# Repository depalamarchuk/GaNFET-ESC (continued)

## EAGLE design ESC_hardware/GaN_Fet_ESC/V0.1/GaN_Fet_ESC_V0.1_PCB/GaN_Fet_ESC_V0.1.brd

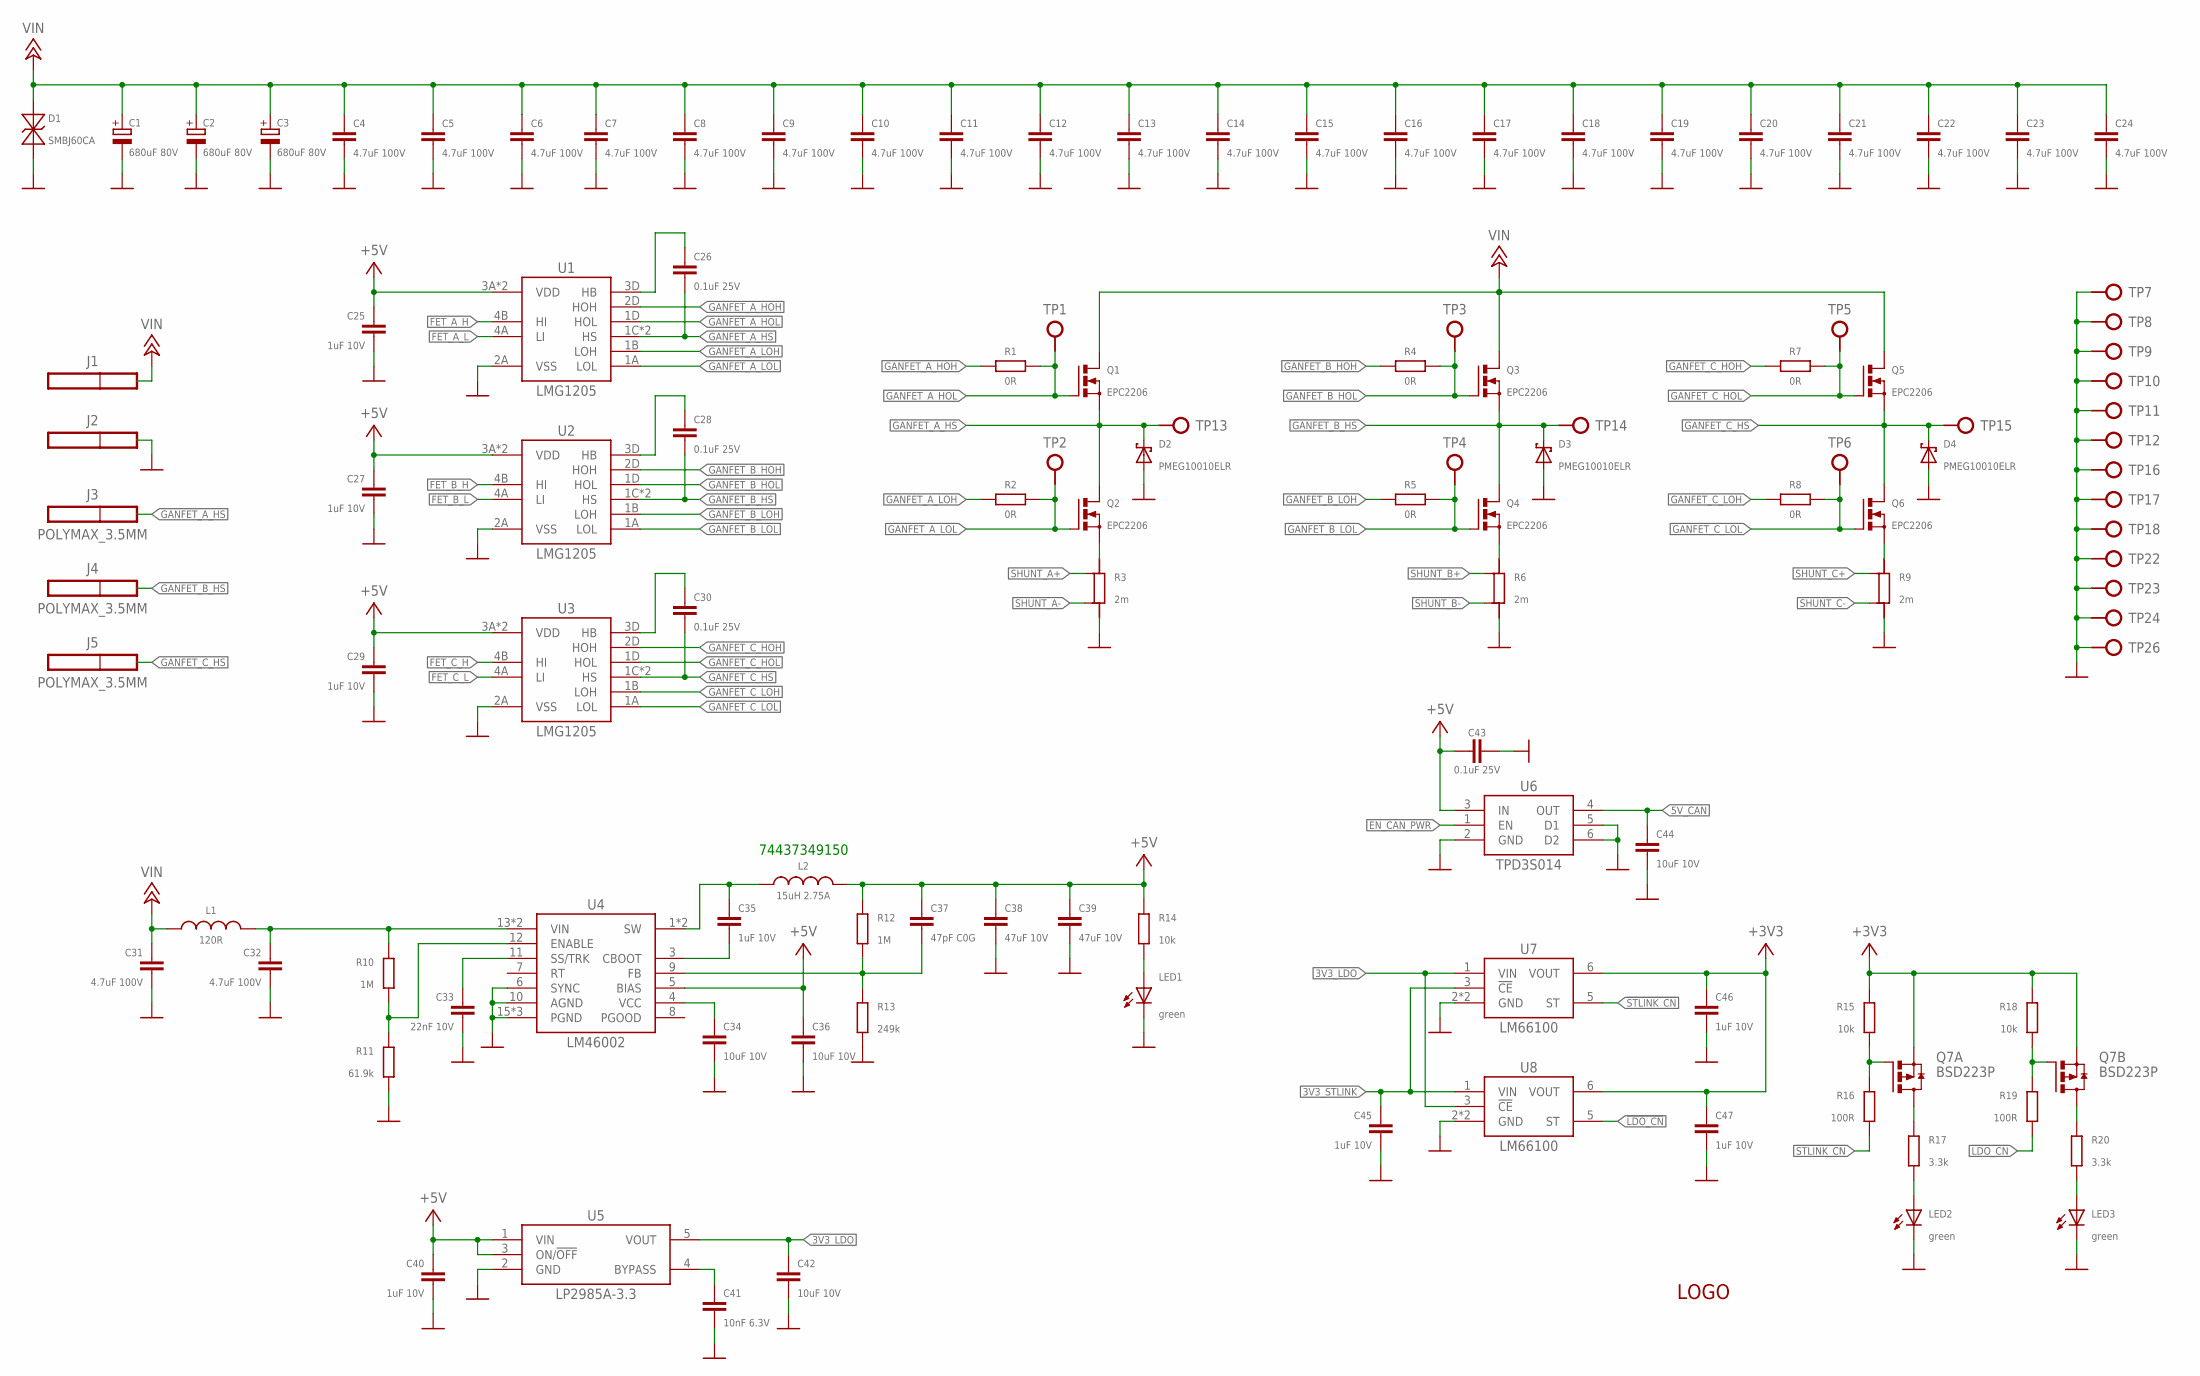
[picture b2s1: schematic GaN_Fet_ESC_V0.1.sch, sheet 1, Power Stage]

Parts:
C1: 680uF 80V; C_7.50_16_26.5_1
C2: 680uF 80V; C_7.50_16_26.5_2
C3: 680uF 80V; C_7.50_16_26.5_3
C4, C5, C6, C7, C8, C9, C10, C11, C12, C13, C14, C15, C16, C17, C18, C19, C20, C21, C22, C23, C24, C31, C32: 4.7uF 100V; C1210
C25, C27, C29, C35, C40, C45, C46, C47: 1uF 10V; C0402
C26, C28, C30, C43: 0.1uF 25V; C0402
C33: 22nF 10V; C0402
C34, C36, C42, C44: 10uF 10V; C0603
C37: 47pF C0G; C0402
C38, C39: 47uF 10V; C1206
C41: 10nF 6.3V; C0402
D1: SMBJ60CA; DO214AA(SMB)
D2, D3, D4: PMEG10010ELR; SOD123F
J1, J2: PIN_14X10; 4X10SMD
J3, J4, J5: POLYMAX_3.5MM
L1: 120R; L1206
L2: 15uH 2.75A; WURTH_6.6X6.6
LED1, LED2, LED3: green; CHIP-LED0603
Q1, Q2, Q3, Q4, Q5, Q6: EPC2206
Q7: BSD223P; SC-70-6
R1, R2, R4, R5, R7, R8: 0R; R0402
R3, R6, R9: 2m; CSS2H-2512
R10: 1M; R0603
R11: 61.9k; R0603
R12: 1M; R0402
R13: 249k; R0402
R14, R15, R18: 10k; R0402
R16, R19: 100R; R0402
R17, R20: 3.3k; R0402
TP1, TP2, TP3, TP4, TP5, TP6, TP13, TP14, TP15: TESTPOINT/0.9MM; 0.9MM
TP7, TP8, TP9, TP10, TP11, TP12, TP16, TP17, TP18, TP22, TP23, TP24, TP26: TESTPOINT0.5MM; 0.5MM
U1, U2, U3: LMG1205
U4: LM46002; TSS0P16-PAD
U5: LP2985A-3.3; SOT-23-5
U6: TPD3S014; SOT-23-6
U7, U8: LM66100; SC-70-6
U$1: LOGO

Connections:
3V3_LDO: C42.1, U5.5 (VOUT), U7.1 (VIN), U8.3 (!CE)
3V3_STLINK: C45.1, U7.3 (!CE), U8.1 (VIN); also elsewhere on the board
5V_CAN: C44.1, U6.4 (OUT); also elsewhere on the board
5V_VCC: C34.1, U4.4 (VCC)
5V_VIN: C32.1, L1.2, R10.2, U4.13 (VIN), U4.14 (VIN)
!LDO_CN: R19.1, U8.5 (ST)
!STLINK_CN: R16.1, U7.5 (ST)
+3V3: C46.1, C47.1, Q7.1 (S), Q7.4 (S), R15.2, R18.2, U7.6 (VOUT), U8.6 (VOUT); also elsewhere on the board
+5V: C25.1, C27.1, C29.1, C36.1, C37.1, C38.1, C39.1, C40.1, C43.1, L2.2, R12.2, R14.2, U1.3A (VDD), U1.4C (VDD), U2.3A (VDD), U2.4C (VDD), U3.3A (VDD), U3.4C (VDD), U4.5 (BIAS), U5.1 (VIN), U5.3 (ON/!OFF), U6.3 (IN); also elsewhere on the board
CBOOT: C35.2, U4.3 (CBOOT)
ENABLE: R10.1, R11.2, U4.12 (ENABLE)
EN_CAN_PWR: U6.1 (EN)
FB: C37.2, R12.1, R13.2, U4.9 (FB)
FET_A_H: U1.4B (HI); also elsewhere on the board
FET_A_L: U1.4A (LI); also elsewhere on the board
FET_B_H: U2.4B (HI); also elsewhere on the board
FET_B_L: U2.4A (LI); also elsewhere on the board
FET_C_H: U3.4B (HI); also elsewhere on the board
FET_C_L: U3.4A (LI); also elsewhere on the board
GANFET_A_HB: C26.1, U1.3D (HB)
GANFET_A_HOH: R1.1, U1.2D (HOH)
GANFET_A_HOL: Q1.1 (G), R1.2, TP1.P$1, U1.1D (HOL)
GANFET_A_HS: C26.2, D2.C, J3.1, Q1.2 (S), Q1.5 (S), Q1.6 (S), Q1.9 (S), Q1.10 (S), Q1.13 (S), Q1.14 (S), Q1.17 (S), Q1.18 (S), Q1.21 (S), Q1.22 (S), Q1.25 (S), Q1.26 (S), Q1.29 (S), Q1.30 (S), Q2.3 (D), Q2.4 (D), Q2.7 (D), Q2.8 (D), Q2.11 (D), Q2.12 (D), Q2.15 (D), Q2.16 (D), Q2.19 (D), Q2.20 (D), Q2.23 (D), Q2.24 (D), Q2.27 (D), Q2.28 (D), TP13.P$1, U1.1C (HS), U1.4D (HS); also elsewhere on the board
GANFET_A_LOH: R2.1, U1.1B (LOH)
GANFET_A_LOL: Q2.1 (G), R2.2, TP2.P$1, U1.1A (LOL)
GANFET_A_SHUNT: Q2.2 (S), Q2.5 (S), Q2.6 (S), Q2.9 (S), Q2.10 (S), Q2.13 (S), Q2.14 (S), Q2.17 (S), Q2.18 (S), Q2.21 (S), Q2.22 (S), Q2.25 (S), Q2.26 (S), Q2.29 (S), Q2.30 (S), R3.1
GANFET_B_HB: C28.1, U2.3D (HB)
GANFET_B_HOH: R4.1, U2.2D (HOH)
GANFET_B_HOL: Q3.1 (G), R4.2, TP3.P$1, U2.1D (HOL)
GANFET_B_HS: C28.2, D3.C, J4.1, Q3.2 (S), Q3.5 (S), Q3.6 (S), Q3.9 (S), Q3.10 (S), Q3.13 (S), Q3.14 (S), Q3.17 (S), Q3.18 (S), Q3.21 (S), Q3.22 (S), Q3.25 (S), Q3.26 (S), Q3.29 (S), Q3.30 (S), Q4.3 (D), Q4.4 (D), Q4.7 (D), Q4.8 (D), Q4.11 (D), Q4.12 (D), Q4.15 (D), Q4.16 (D), Q4.19 (D), Q4.20 (D), Q4.23 (D), Q4.24 (D), Q4.27 (D), Q4.28 (D), TP14.P$1, U2.1C (HS), U2.4D (HS); also elsewhere on the board
GANFET_B_LOH: R5.1, U2.1B (LOH)
GANFET_B_LOL: Q4.1 (G), R5.2, TP4.P$1, U2.1A (LOL)
GANFET_B_SHUNT: Q4.2 (S), Q4.5 (S), Q4.6 (S), Q4.9 (S), Q4.10 (S), Q4.13 (S), Q4.14 (S), Q4.17 (S), Q4.18 (S), Q4.21 (S), Q4.22 (S), Q4.25 (S), Q4.26 (S), Q4.29 (S), Q4.30 (S), R6.1
GANFET_C_HB: C30.1, U3.3D (HB)
GANFET_C_HOH: R7.1, U3.2D (HOH)
GANFET_C_HOL: Q5.1 (G), R7.2, TP5.P$1, U3.1D (HOL)
GANFET_C_HS: C30.2, D4.C, J5.1, Q5.2 (S), Q5.5 (S), Q5.6 (S), Q5.9 (S), Q5.10 (S), Q5.13 (S), Q5.14 (S), Q5.17 (S), Q5.18 (S), Q5.21 (S), Q5.22 (S), Q5.25 (S), Q5.26 (S), Q5.29 (S), Q5.30 (S), Q6.3 (D), Q6.4 (D), Q6.7 (D), Q6.8 (D), Q6.11 (D), Q6.12 (D), Q6.15 (D), Q6.16 (D), Q6.19 (D), Q6.20 (D), Q6.23 (D), Q6.24 (D), Q6.27 (D), Q6.28 (D), TP15.P$1, U3.1C (HS), U3.4D (HS); also elsewhere on the board
GANFET_C_LOH: R8.1, U3.1B (LOH)
GANFET_C_LOL: Q6.1 (G), R8.2, TP6.P$1, U3.1A (LOL)
GANFET_C_SHUNT: Q6.2 (S), Q6.5 (S), Q6.6 (S), Q6.9 (S), Q6.10 (S), Q6.13 (S), Q6.14 (S), Q6.17 (S), Q6.18 (S), Q6.21 (S), Q6.22 (S), Q6.25 (S), Q6.26 (S), Q6.29 (S), Q6.30 (S), R9.1
GND: C1.-, C2.-, C3.-, C4.2, C5.2, C6.2, C7.2, C8.2, C9.2, C10.2, C11.2, C12.2, C13.2, C14.2, C15.2, C16.2, C17.2, C18.2, C19.2, C20.2, C21.2, C22.2, C23.2, C24.2, C25.2, C27.2, C29.2, C31.2, C32.2, C33.2, C34.2, C36.2, C38.2, C39.2, C40.2, C41.2, C42.2, C43.2, C44.2, C45.2, C46.2, C47.2, D1.K (C), D2.A, D3.A, D4.A, J2.1, LED1.C, LED2.C, LED3.C, R3.2, R6.2, R9.2, R11.1, R13.1, TP7.P$1, TP8.P$1, TP9.P$1, TP10.P$1, TP11.P$1, TP12.P$1, TP16.P$1, TP17.P$1, TP18.P$1, TP22.P$1, TP23.P$1, TP24.P$1, TP26.P$1, U1.2A (VSS), U2.2A (VSS), U3.2A (VSS), U4.6 (SYNC), U4.10 (AGND), U4.15 (PGND), U4.16 (PGND), U4.PAD (PGND), U5.2 (GND), U6.2 (GND), U6.5 (D1), U6.6 (D2), U7.2 (GND), U7.4 (GND), U8.2 (GND), U8.4 (GND); also elsewhere on the board
LDO_BYPASS: C41.1, U5.4 (BYPASS)
unnamed: LED3.A, R20.1
unnamed: LED2.A, R17.1
unnamed: LED1.A, R14.1
unnamed: Q7.3 (D), R17.2
unnamed: Q7.6 (D), R20.2
unnamed: Q7.2 (G), R15.1, R16.2
unnamed: Q7.5 (G), R18.1, R19.2
SHUNT_A+: R3.1_SENSE (1K); also elsewhere on the board
SHUNT_A-: R3.2_SENSE (2K); also elsewhere on the board
SHUNT_B+: R6.1_SENSE (1K); also elsewhere on the board
SHUNT_B-: R6.2_SENSE (2K); also elsewhere on the board
SHUNT_C+: R9.1_SENSE (1K); also elsewhere on the board
SHUNT_C-: R9.2_SENSE (2K); also elsewhere on the board
SS: C33.1, U4.11 (SS/TRK)
SW: C35.1, L2.1, U4.1 (SW), U4.2 (SW)
VIN: C1.+, C2.+, C3.+, C4.1, C5.1, C6.1, C7.1, C8.1, C9.1, C10.1, C11.1, C12.1, C13.1, C14.1, C15.1, C16.1, C17.1, C18.1, C19.1, C20.1, C21.1, C22.1, C23.1, C24.1, C31.1, D1.A, J1.1, L1.1, Q1.3 (D), Q1.4 (D), Q1.7 (D), Q1.8 (D), Q1.11 (D), Q1.12 (D), Q1.15 (D), Q1.16 (D), Q1.19 (D), Q1.20 (D), Q1.23 (D), Q1.24 (D), Q1.27 (D), Q1.28 (D), Q3.3 (D), Q3.4 (D), Q3.7 (D), Q3.8 (D), Q3.11 (D), Q3.12 (D), Q3.15 (D), Q3.16 (D), Q3.19 (D), Q3.20 (D), Q3.23 (D), Q3.24 (D), Q3.27 (D), Q3.28 (D), Q5.3 (D), Q5.4 (D), Q5.7 (D), Q5.8 (D), Q5.11 (D), Q5.12 (D), Q5.15 (D), Q5.16 (D), Q5.19 (D), Q5.20 (D), Q5.23 (D), Q5.24 (D), Q5.27 (D), Q5.28 (D); also elsewhere on the board

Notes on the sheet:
74437349150

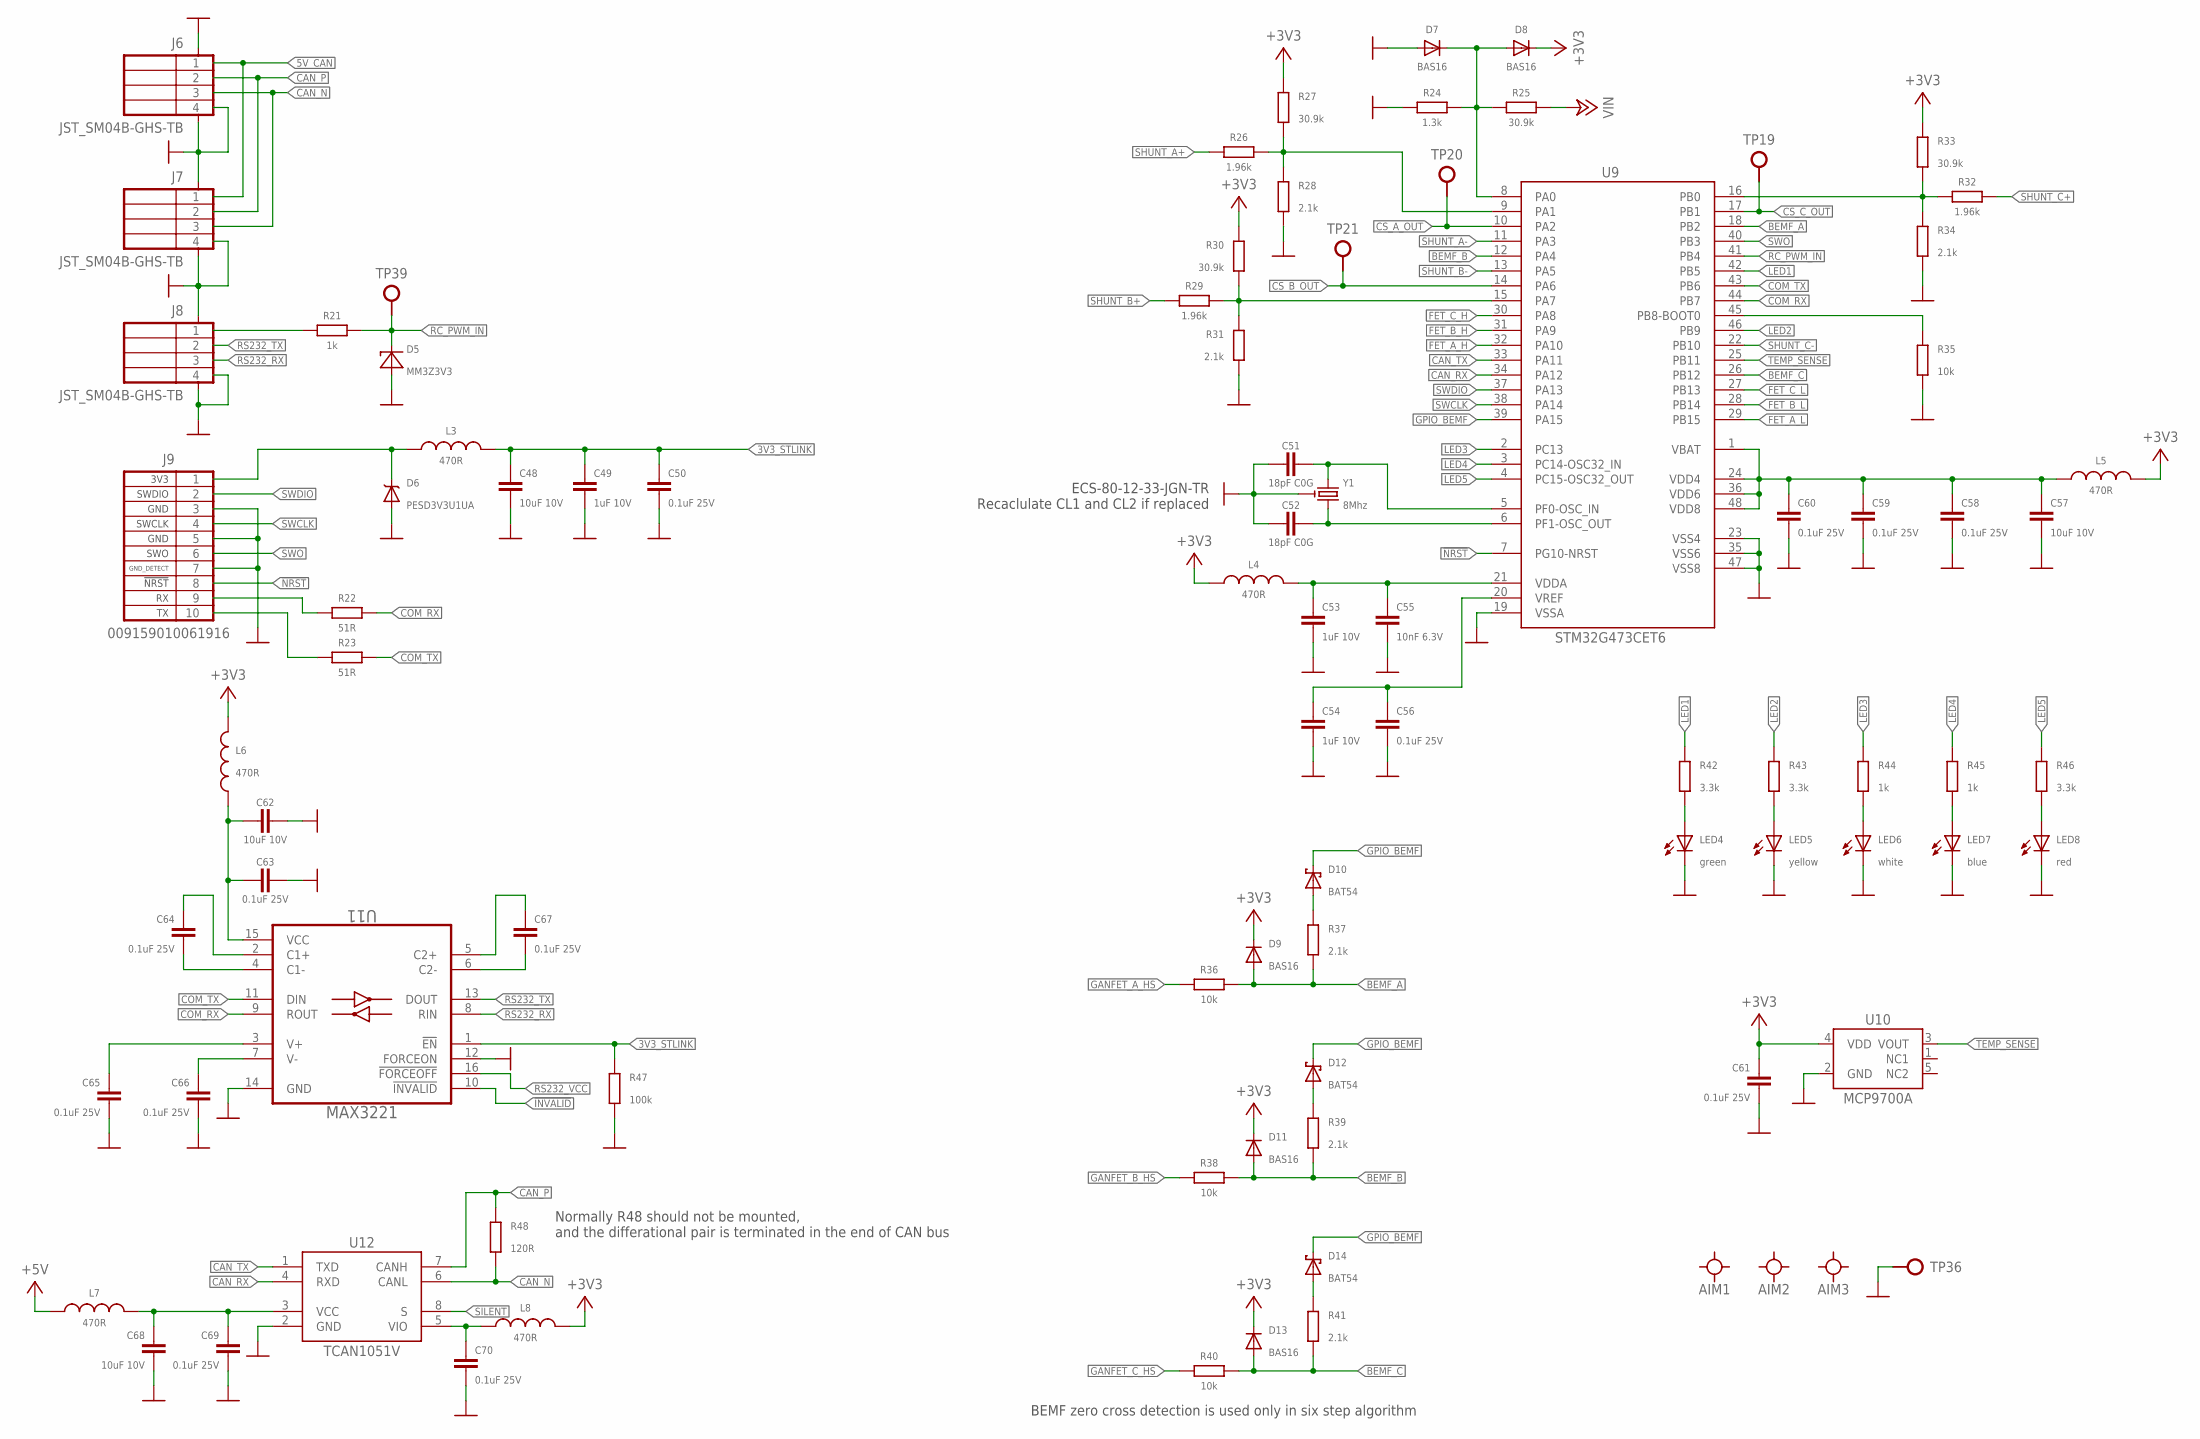
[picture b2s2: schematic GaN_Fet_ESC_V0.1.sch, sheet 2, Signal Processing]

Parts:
AIM1, AIM2, AIM3: AIM_1_MM
C48, C57, C62, C68: 10uF 10V; C0603
C49, C53, C54: 1uF 10V; C0402
C50, C56, C58, C59, C60, C61, C63, C64, C65, C66, C67, C69, C70: 0.1uF 25V; C0402
C51, C52: 18pF C0G; C0402
C55: 10nF 6.3V; C0402
D5: MM3Z3V3; SOD323F
D6: PESD3V3U1UA; SOD323F
D7, D8, D9, D11, D13: BAS16; SOD523
D10, D12, D14: BAT54; SOD523
J6, J7, J8: JST_SM04B-GHS-TB
J9: 009159010061916
L3, L4, L5, L6, L7, L8: 470R; L0603
LED4: green; CHIP-LED0603
LED5: yellow; CHIP-LED0603
LED6: white; CHIP-LED0603
LED7: blue; CHIP-LED0603
LED8: red; CHIP-LED0603
R21, R44, R45: 1k; R0402
R22, R23: 51R; R0402
R24: 1.3k; R0603
R25: 30.9k; R0603
R26, R29, R32: 1.96k; R0402
R27, R30, R33: 30.9k; R0402
R28, R31, R34, R37, R39, R41: 2.1k; R0402
R35, R36, R38, R40: 10k; R0402
R42, R43, R46: 3.3k; R0402
R47: 100k; R0402
R48: 120R; R0805
TP19, TP20, TP21, TP39: TESTPOINT/0.9MM; 0.9MM
TP36: TESTPOINT0.5MM; 0.5MM
U9: STM32G473CET6; LQFP-48
U10: MCP9700A; SC-70-5
U11: MAX3221; TSS0P16
U12: TCAN1051V; SOIC-8
Y1: 8Mhz; CRYSTAL_SMD_3.2X2.5MM

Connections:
3V3_STLINK: C48.1, C49.1, C50.1, L3.1, R47.2, U11.1 (!EN); also elsewhere on the board
5V_CAN: J6.1, J7.1; also elsewhere on the board
!INVALID: U11.10 (!INVALID)
!NRST: J9.8, U9.7 (PG10-NRST)
+3V3: C61.1, D8.C, D9.C, D11.C, D13.C, L4.1, L5.2, L6.1, L8.2, R27.2, R30.2, R33.2, U10.4 (VDD); also elsewhere on the board
+5V: L7.1; also elsewhere on the board
BEMF_A: D9.A, R36.2, R37.1, U9.18 (PB2)
BEMF_B: D11.A, R38.2, R39.1, U9.12 (PA4)
BEMF_C: D13.A, R40.2, R41.1, U9.26 (PB12)
BOOT0: R35.2, U9.45 (PB8-BOOT0)
C1+: C64.1, U11.2 (C1+)
C1-: C64.2, U11.4 (C1-)
C2+: C67.1, U11.5 (C2+)
C2-: C67.2, U11.6 (C2-)
CAN_N: J6.3, J7.3, R48.1, U12.6 (CANL)
CAN_P: J6.2, J7.2, R48.2, U12.7 (CANH)
CAN_RX: U9.34 (PA12), U12.4 (RXD)
CAN_TX: U9.33 (PA11), U12.1 (TXD)
CAN_VCC: C68.1, C69.1, L7.2, U12.3 (VCC)
CAN_VIO: C70.1, L8.1, U12.5 (VIO)
COM_RX: R22.1, U9.44 (PB7), U11.9 (ROUT)
COM_TX: R23.1, U9.43 (PB6), U11.11 (DIN)
CS_A_OUT: TP20.P$1, U9.10 (PA2)
CS_B_OUT: TP21.P$1, U9.14 (PA6)
CS_C_OUT: TP19.P$1, U9.17 (PB1)
FET_A_H: U9.32 (PA10); also elsewhere on the board
FET_A_L: U9.29 (PB15); also elsewhere on the board
FET_B_H: U9.31 (PA9); also elsewhere on the board
FET_B_L: U9.28 (PB14); also elsewhere on the board
FET_C_H: U9.30 (PA8); also elsewhere on the board
FET_C_L: U9.27 (PB13); also elsewhere on the board
GANFET_A_HS: R36.1; also elsewhere on the board
GANFET_B_HS: R38.1; also elsewhere on the board
GANFET_C_HS: R40.1; also elsewhere on the board
GND: C48.2, C49.2, C50.2, C51.1, C52.1, C53.2, C54.2, C55.2, C56.2, C57.2, C58.2, C59.2, C60.2, C61.2, C62.2, C63.2, C65.2, C66.2, C68.2, C69.2, C70.2, D5.A, D6.A, D7.A, J6.4, J6.5, J6.6, J7.4, J7.5, J7.6, J8.4, J8.5, J8.6, J9.3, J9.5, J9.7, LED4.C, LED5.C, LED6.C, LED7.C, LED8.C, R24.1, R28.1, R31.1, R34.1, R35.1, R47.1, TP36.P$1, U9.19 (VSSA), U9.23 (VSS4), U9.35 (VSS6), U9.47 (VSS8), U10.2 (GND), U11.12 (FORCEON), U11.14 (GND), U12.2 (GND), Y1.2 (3), Y1.4 (3); also elsewhere on the board
GPIO_BEMF: D10.C, D12.C, D14.C, U9.39 (PA15)
LED1: R42.2, U9.42 (PB5)
LED2: R43.2, U9.46 (PB9)
LED3: R44.2, U9.2 (PC13)
LED4: R45.2, U9.3 (PC14-OSC32_IN)
LED5: R46.2, U9.4 (PC15-OSC32_OUT)
MCU_VDD: C57.1, C58.1, C59.1, C60.1, L5.1, U9.1 (VBAT), U9.24 (VDD4), U9.36 (VDD6), U9.48 (VDD8)
MCU_VDDA: C53.1, C55.1, L4.2, U9.21 (VDDA)
MCU_VREF: C54.1, C56.1, U9.20 (VREF)
unnamed: LED5.A, R43.1
unnamed: J9.9, R22.2
unnamed: LED4.A, R42.1
unnamed: LED7.A, R45.1
unnamed: LED8.A, R46.1
unnamed: J8.1, R21.2
unnamed: D12.A, R39.2
unnamed: C51.2, U9.5 (PF0-OSC_IN), Y1.1
unnamed: C52.2, U9.6 (PF1-OSC_OUT), Y1.3 (2)
unnamed: D10.A, R37.2
unnamed: D14.A, R41.2
unnamed: D6.C, J9.1, L3.2
unnamed: J9.10, R23.2
unnamed: LED6.A, R44.1
OPAMP1+: R26.2, R27.1, R28.2, U9.9 (PA1)
OPAMP2+: R29.2, R30.1, R31.2, U9.15 (PA7)
OPAMP3+: R32.2, R33.1, R34.2, U9.16 (PB0)
RC_PWM_IN: D5.C, R21.1, TP39.P$1, U9.41 (PB4)
RS232_RX: J8.3, U11.8 (RIN)
RS232_TX: J8.2, U11.13 (DOUT)
RS232_VCC: C62.1, C63.1, L6.2, U11.15 (VCC), U11.16 (!FORCEOFF)
SHUNT_A+: R26.1; also elsewhere on the board
SHUNT_A-: U9.11 (PA3); also elsewhere on the board
SHUNT_B+: R29.1; also elsewhere on the board
SHUNT_B-: U9.13 (PA5); also elsewhere on the board
SHUNT_C+: R32.1; also elsewhere on the board
SHUNT_C-: U9.22 (PB10); also elsewhere on the board
SILENT: U12.8 (S)
SWCLK: J9.4, U9.38 (PA14)
SWDIO: J9.2, U9.37 (PA13)
SWO: J9.6, U9.40 (PB3)
TEMP_SENSE: U9.25 (PB11), U10.3 (VOUT)
V+: C65.1, U11.3 (V+)
V-: C66.1, U11.7 (V-)
VIN: R25.2; also elsewhere on the board
VIN_SENSE: D7.C, D8.A, R24.2, R25.1, U9.8 (PA0)

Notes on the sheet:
!NRST
GND_DETECT
3V3
SWDIO
SWCLK
SWO
GND
Normally R48 should not be mounted, and the differational pair is terminated in the end of CAN bus
BEMF zero cross detection is used only in six step algorithm
ECS-80-12-33-JGN-TR Recaclulate CL1 and CL2 if replaced

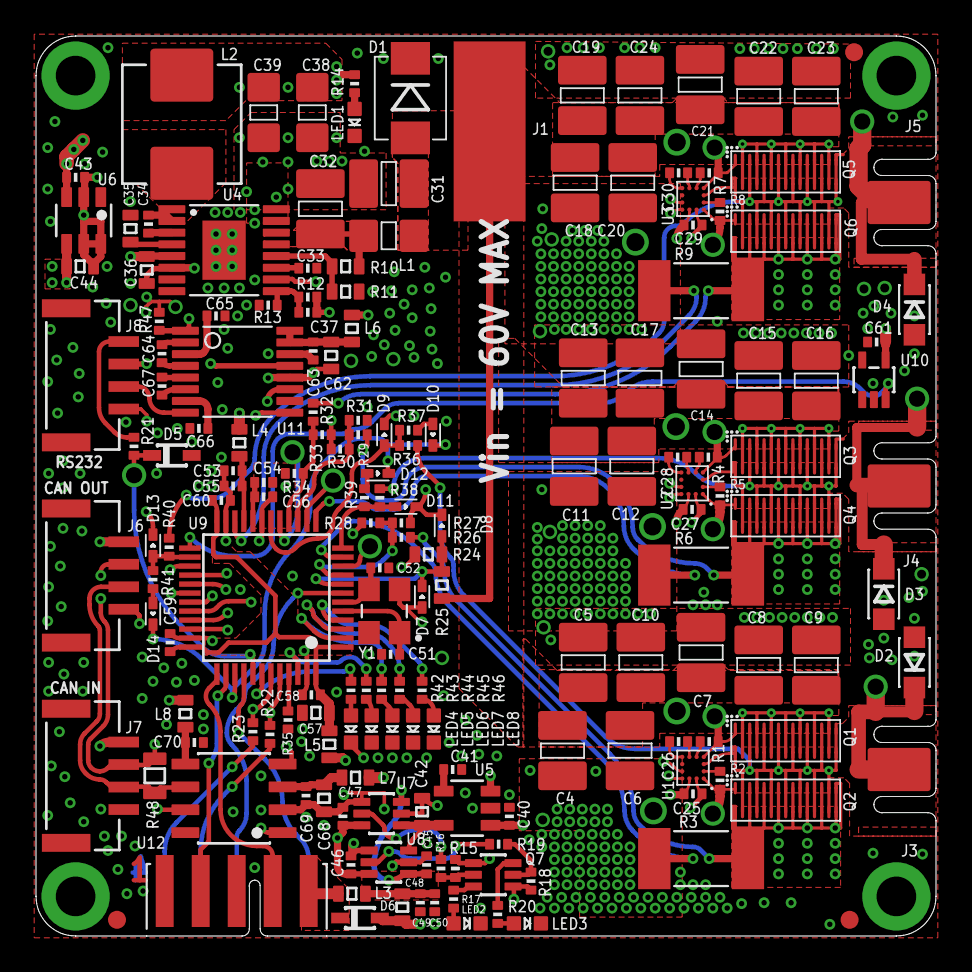
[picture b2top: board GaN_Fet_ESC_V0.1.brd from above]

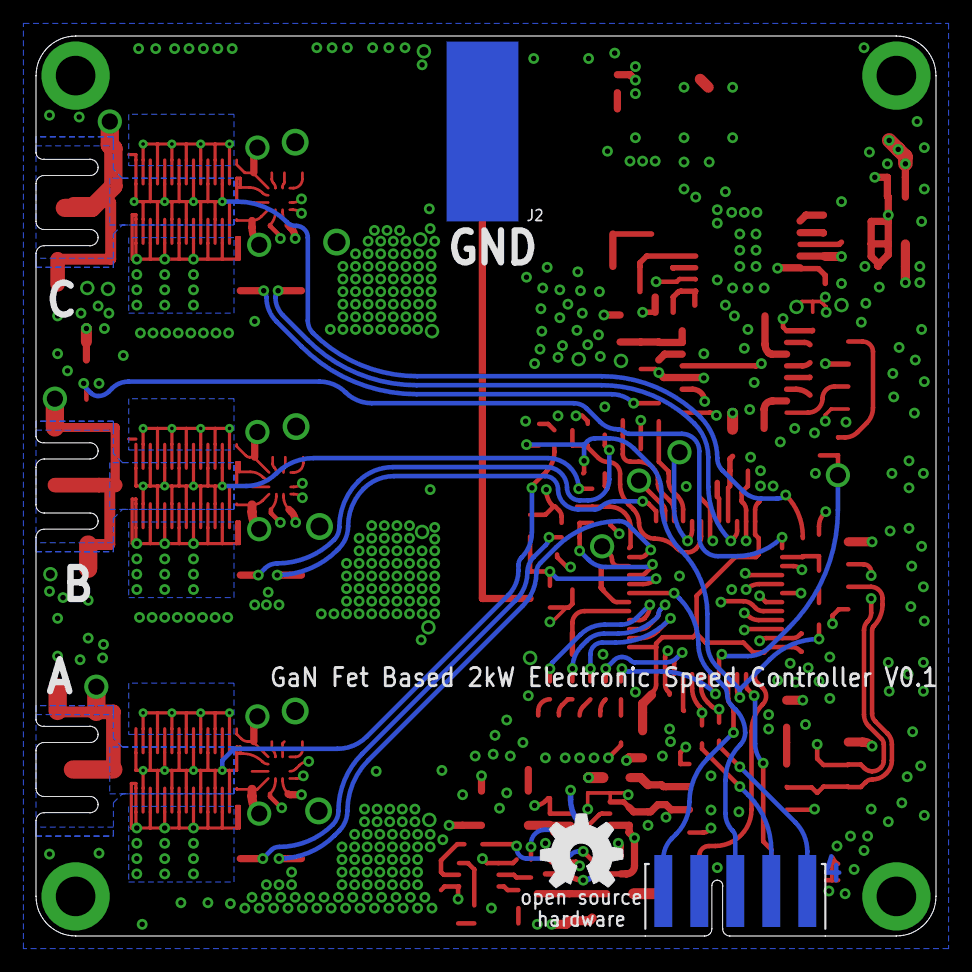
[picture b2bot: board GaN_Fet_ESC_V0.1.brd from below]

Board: 4 copper layers, 50.0 x 50.0 mm, 208 parts (2 on the bottom side), 114 nets.

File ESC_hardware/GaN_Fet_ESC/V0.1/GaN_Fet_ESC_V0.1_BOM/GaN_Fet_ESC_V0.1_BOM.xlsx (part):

|  | GaN Fet Electronic Speed Controller PCB BOM
Qty | Parts | Value | Description | Case | Supplier 1 | Supplier ID 1 | Manufacturer 1 | Manufacturer ID 1 | Supplier 2 | Supplier ID 2 | Manufacturer 2 | Manufacturer ID 2 | Alternative manufacturers. 1 – All 2 – First ask 3 – do not replace
2 | C51, C52 | 18pF C0G | ±5% ≥6.3V Ceramic Capacitor C0G/NP0 | C0402 | Mouser | 80-C0402C180J8G | KEMET | C0402C180J8GACTU | Mouser | 81-GJM1555C1H180GB01 | Murata Electronics | GJM1555C1H180GB01D | 1
1 | C37 | 47pF C0G | ±5% ≥10V Ceramic Capacitor C0G/NP0 | C0402 | Mouser | 80-C0402C470J5G | KEMET | C0402C470J5GACTU | Mouser | 603-CC402JRNPO9BN470 | Yageo | CC0402JRNPO9BN470 | 1
2 | C41, C55 | 10nF 6.3V | ±10% ≥6.3V Ceramic Capacitor X7R | C0402 | Mouser | 80-C0402C103K3R | KEMET | C0402C103K3RACTU | Mouser | 81-GCM155R71H103KA5D | Murata Electronics | GCM155R71H103KA55D | 1
1 | C33 | 22nF 10V | ±10% ≥10V Ceramic Capacitor X7R | C0402 | Mouser | 963-EMK105B7223KV-F | Taiyo Yuden | EMK105B7223KV-F | Mouser | 603-CC402KRX7R7BB223 | Yageo | CC0402KRX7R7BB223 | 1
17 | C26, C28, C30, C43, C50, C56, C58, C59, C60, C61, C63, C64, C65, C66, C67, C69,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 | 0.1uF 25V | ±10% ≥25V Ceramic Capacitor X7R | C0402 | Mouser | 81-GRM155R71E104KE4D | Murata Electronics | GRM155R71E104KE14D | Mouser | 603-CS0402KRX78BB104 | Yageo | CS0402KRX7R8BB104 | 1
11 | C25, C27, C29, C35, C40, C45, C46, C47, C49, C53, C54 | 1uF 10V | ±10% ≥10V Ceramic Capacitor X7S | C0402 | Mouser | 81-GCM155C71A105KE8D | Murata Electronics | GCM155C71A105KE38D | Mouser | 81-GRM155C71A105KE1J | Murata Electronics | GRM155C71A105KE11J | 1
8 | C34, C36, C42, C44, C48, C57, C62, C68 | 10uF 10V | ±10% ≥10V Ceramic Capacitor X7T | C0603 | Mouser | 81-GRM188D71A106KA3 | Murata Electronics | GRM188D71A106KA73D | Mouser | 81-ZRB18AD71A106KE1L | Murata Electronics | ZRB18AD71A106KE01L | 1
23 | C4, C5, C6, C7, C8, C9, C10, C11, C12, C13, C14, C15, C16, C17, C18, C19, C20, 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 | 4.7uF 100V | ±10% ≥100V Ceramic Capacitor X7S | C1210 | Mouser | 963-HMK325C7475KM-PE | Taiyo Yuden | HMK325C7475KM-PE | Mouser | 963-HMK325C7475KN-TE | Taiyo Yuden | HMK325C7475KN-TE | 1
2 | C38, C39 | 47uF 10V | ±10% ≥10V Ceramic Capacitor X5R | C1206 | Mouser | 81-GRM31CR61A476KE5L | Murata Electronics | GRM31CR61A476KE15L | Mouser | 81-GRM31CR61A476KE5K | Murata Electronics | GRM31CR61A476KE15K | 1
3 | C1, C2, C3 | 680uF 80V | 680µF 80V Aluminum Electrolytic Capacitors Radial, Can 10000 Hrs @ 105°C | C_7.50_16_26.5 | Mouser | 661-EKZN800E681ML25S | United Chemi-Con | EKZN800ELL681ML25S | Digi-Key | 565-4121-ND | United Chemi-Con | EKZN800ELL681ML25S | 2
6 | R1, R2, R4, R5, R7, R8 | 0R | ±1% 100 mW 50V Chip Resistor 0402, AEC-Q200 | R0402 | Mouser | 660-RK73Z1ETTP | KOA Speer | RK73Z1ETTP | Mouser | 667-ERJ-2GE0R00X | Panasonic | ERJ-2GE0R00X | 1
2 | R22, R23 | 51R | ±1% 100 mW 50V Chip Resistor 0402, AEC-Q200 | R0402 | Mouser | 660-RK73H1ETTP51R0F | KOA Speer | RK73H1ETTP51R0F | Mouser | 667-ERJ-2RKF51R0X | Panasonic | ERJ-2RKF51R0X | 1
2 | R16, R19 | 100R | ±1% 62.5 mW 50V Chip Resistor 0402, AEC-Q200 | R0402 | Mouser | 660-RK73H1ETTP1000F | KOA Speer | RK73H1ETTP1000F | Mouser | 660-RK73H1ETTPB1000F | KOA Speer | RK73H1ETTPB1000F | 1
1 | R48 | 120R | ±1% 0.25 mW 50V Chip Resistor 0805, AEC-Q200 | R0805 | Mouser | 660-RK73H2ATTD1200F | KOA Speer | RK73H2ATTD1200F | Mouser | 660-RK73H2ATTDD1200F | KOA Speer | RK73H2ATTDD1200F | 1
3 | R21, R44, R45 | 1k | ±1% 62.5 mW 50V Chip Resistor 0402, AEC-Q200 | R0402 | Mouser | 660-RK73H1ETTP1001F | KOA Speer | RK73H1ETTP1001F | Mouser | 71-CRCW0402-1.0K-E3 | Vishay / Dale | CRCW04021K00FKED | 1
1 | R24 | 1.3k | ±1% 100 mW 75V Chip Resistor 0603, AEC-Q200 | R0603 | Mouser | 660-RK73H1JTTD1301F | KOA Speer | RK73H1JTTD1301F | Mouser | 791-WR06X1301FTL | Walsin | WR06X1301FTL | 1
3 | R26, R29, R32 | 1.96k | ±1% 62.5 mW 50V Chip Resistor 0402, AEC-Q200 | R0402 | Mouser | 660-RK73H1ETTP1961F | KOA Speer | RK73H1ETTP1961F | Mouser | 667-ERJ-2RKF1961X | Panasonic | ERJ-2RKF1961X | 1
6 | R28, R31, R34, R37, R39, R41 | 2.1k | ±1% 62.5 mW 50V Chip Resistor 0402, AEC-Q200 | R0402 | Mouser | 660-RK73H1ETTP2101F | KOA Speer | RK73H1ETTP2101F | Mouser | 667-ERJ-2RKF2101X | Panasonic | ERJ-2RKF2101X | 1
5 | R17, R20, R42, R43, R46 | 3.3k | ±1% 62.5 mW 50V Chip Resistor 0402, AEC-Q200 | R0402 | Mouser | 660-RK73H1ETTP3301F | KOA Speer | RK73H1ETTP3301F | Mouser | 71-CRCW0402-3.3K-E3 | Vishay / Dale | CRCW04023K30FKED | 1
7 | R14, R15, R18, R35, R36, R38, R40 | 10k | ±1% 62.5 mW 50V Chip Resistor 0402, AEC-Q200 | R0402 | Mouser | 660-RK73H1ETTP1002F | KOA Speer | RK73H1ETTP1002F | Mouser | 667-ERJ-2RKF1002X | Panasonic | ERJ-2RKF1002X | 1
3 | R27, R30, R33 | 30.9k | ±1% 62.5 mW 50V Chip Resistor 0402, AEC-Q200 | R0402 | Mouser | 660-RK73H1ETTP3092F | KOA Speer | RK73H1ETTP3092F | Mouser | 71-CRCW0402-30.9K-E3 | Vishay / Dale | CRCW040230K9FKED | 1
1 | R25 | 30.9k | ±1% 100 mW 75V Chip Resistor 0603, AEC-Q200 | R0603 | Mouser | 660-RK73H1JTTD3092F | KOA Speer | RK73H1JTTD3092F | Mouser | 603-AC0603FR-0730K9L | Yageo | AC0603FR-0730K9L | 1
1 | R11 | 61.9k | ±1% 100 mW 75V Chip Resistor 0603, AEC-Q200 | R0603 | Mouser | 660-RK73H1JTTD6192F | KOA Speer | RK73H1JTTD6192F | Mouser | 660-RK73H1JTTDD6192F | KOA Speer | RK73H1JTTDD6192F | 1
1 | R47 | 100k | ±1% 62.5 mW 50V Chip Resistor 0402, AEC-Q200 | R0402 | Mouser | 660-RK73H1ETTPS1003F | KOA Speer | RK73H1ETTPS1003F | Mouser | 71-CRCW0402-100K-E3 | Vishay / Dale | CRCW0402100KFKED | 1
1 | R13 | 249k | ±1% 62.5 mW 50V Chip Resistor 0402, AEC-Q200 | R0402 | Mouser | 660-RK73H1ETTP2493F | KOA Speer | RK73H1ETTP2493F | Mouser | 667-ERJ-2RKF2493X | Panasonic | ERJ-2RKF2493X | 1
1 | R12 | 1M | ±1% 62.5 mW 50V Chip Resistor 0402, AEC-Q200 | R0402 | Mouser | 660-RK73H1ETTP1004F | KOA Speer | RK73H1ETTP1004F | Mouser | 71-CRCW0402-1.0M-E3 | Vishay / Dale | CRCW04021M00FKED | 1
1 | R10 | 1M | ±1% 100 mW 75V Chip Resistor 0603, AEC-Q200 | R0603 | Mouser | 660-RK73H1JTTD1004F | KOA Speer | RK73H1JTTD1004F | Mouser | 603-AC0603FR-071ML | Yageo | AC0603FR-071ML | 1
3 | R3, R6, R9 | 2m | Current Sense Resistors - SMD 2mOhms 5W 1% AEC-Q200 | CSS2H-2512 | Mouser | 652-CSS2H2512K2L00F | Bourns | CSS2H-2512K-2L00F | Digi-Key | CSS2H-2512K-2L00FCT-ND | Bourns Inc. | CSS2H-2512K-2L00F | 2
1 | L1 | 120R | Ferrite Beads 1206 120ohms ≥3A | L1206 | Mouser | 81-BLM31KN121SZ1L | Murata Electronics | BLM31KN121SZ1L | Mouser | 81-BLM31KN121SH1L | Murata Electronics | BLM31KN121SH1L | 1
6 | L3, L4, L5, L6, L7, L8 | 470R | Ferrite Beads 0603 470ohms | L0603 | Mouser | 81-BLM18KG471SN1D | Murata Electronics | BLM18KG471SN1D | Mouser | 810-MPZ1608B471ATA00 | TDK | MPZ1608B471ATA00 | 1
1 | L2 | 15uH 2.75A | Fixed Inductors WE-LHMI Powr SMD7050 15uH 2.75A 92mOhm | WURTH_6.6X6.6 | Mouser | 710-74437349150 | Wurth Elektronik | 74437349150 | N/A | N/A | N/A | N/A | 3
1 | Y1 | 16Mhz | 8MHz ±20ppm Crystal 12pF 400 Ohms 4-SMD, No Lead | CRYSTAL_SMD_3.2X2.5MM | Mouser | ECS-80-12-33-JGN-TR | ECS | ECS-80-12-33-JGN-TR | Digi-Key | 50-ECS-80-12-33-JGN-CT-ND | ECS Inc. | ECS-80-12-33-JGN-TR | 1
1 | D1 | SMBJ60CA | 96.8V Clamp 6.2A Ipp Tvs Diode Surface Mount SMB | DO214AA(SMB) | Mouser | 621-SMBJ60CA-13-F | Diodes Incorporated | SMBJ60CA-13-F | Digi-Key | SMBJ60CA-FDICT-ND | Diodes Incorporated | SMBJ60CA-13-F | 1
5 | D7, D8, D9, D11, D13 | BAS16 | Diode Standard 100V 200mA (DC) Surface Mount SOD-523 | SOD523 | Mouser | 863-BAS16XV2T1G | ON Semiconductor | BAS16XV2T1G | Digi-Key | BAS16XV2T1GOSCT-ND | ON Semiconductor | BAS16XV2T1G | 1
3 | D10, D12, D14 | BAT54 | Diode Schottky 30V 200mA (DC) Surface Mount SOD-523 | SOD523 | Mouser | 863-BAT54XV2T1G | ON Semiconductor | BAT54XV2T1G | Digi-Key | BAT54XV2T1GOSCT-ND | ON Semiconductor | BAT54XV2T1G | 1
1 | D5 | MM3Z3V3 | Zener Diode 3.3V 300mW ±6% Surface Mount SOD-323 | SOD323F | Mouser | 863-MM3Z3V3T1G | ON Semiconductor | MM3Z3V3T1G | Digi-Key | MM3Z3V3T1GOSCT-ND | ON Semiconductor | MM3Z3V3T1G | 1
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
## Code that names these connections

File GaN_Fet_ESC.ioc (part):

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Mcu.Name=STM32G473C(B-C-E)Tx
Mcu.Package=LQFP48
Mcu.UserName=STM32G473CETx
PA0.GPIOParameters=GPIO_Label
PA0.GPIO_Label=VIN_SENSE
PA0.Mode=IN1-Single-Ended
PA0.Signal=ADC1_IN1
PA1.GPIOParameters=GPIO_Label
PA1.GPIO_Label=SHUNT_A+
PA1.Mode=PGA Connected
PA1.Signal=OPAMP1_VINP
PA10.Signal=S_TIM1_CH3
PA11.Mode=FDCAN_Activate
PA11.Signal=FDCAN1_RX
PA12.Mode=FDCAN_Activate
PA12.Signal=FDCAN1_TX
PA13.Signal=SYS_JTMS-SWDIO
PA14.Signal=SYS_JTCK-SWCLK
PA15.GPIOParameters=GPIO_Label
PA15.GPIO_Label=GPIO_BEMF
PA15.Signal=GPIO_Input
PA2.GPIOParameters=GPIO_Label
PA2.GPIO_Label=CS_A_OUT
PA2.Signal=SharedAnalog_PA2
PA3.GPIOParameters=GPIO_Label
PA3.GPIO_Label=SHUNT_A-
PA3.Mode=PGA Connected
PA3.Signal=OPAMP1_VINM0
PA4.GPIOParameters=GPIO_Label
PA4.GPIO_Label=BEMF_B
PA4.Mode=IN17-Single-Ended
PA4.Signal=ADC2_IN17
PA5.GPIOParameters=GPIO_Label
PA5.GPIO_Label=SHUNT_B-
PA5.Mode=PGA Connected
PA5.Signal=OPAMP2_VINM0
PA6.GPIOParameters=GPIO_Label
PA6.GPIO_Label=CS_B_OUT
PA6.Signal=SharedAnalog_PA6
PA7.GPIOParameters=GPIO_Label
PA7.GPIO_Label=SHUNT_B+
PA7.Mode=PGA Connected
PA7.Signal=OPAMP2_VINP
PA8.Signal=S_TIM1_CH1
PA9.Signal=S_TIM1_CH2
PB0.GPIOParameters=GPIO_Label
PB0.GPIO_Label=SHUNT_C+
PB0.Mode=PGA Connected
PB0.Signal=OPAMP3_VINP
PB1.GPIOParameters=GPIO_Label
PB1.GPIO_Label=CS_C_OUT
PB1.Signal=SharedAnalog_PB1
PB11.GPIOParameters=GPIO_Label
PB11.GPIO_Label=TEMP_SENSE
PB11.Mode=IN14-Single-Ended
PB11.Signal=ADC1_IN14
PB12.GPIOParameters=GPIO_Label
PB12.GPIO_Label=BEMF_C
PB12.Mode=IN11-Single-Ended
PB12.Signal=ADC1_IN11
PB13.Mode=PWM Generation1 CH1 CH1N
PB13.Signal=TIM1_CH1N
PB14.Mode=PWM Generation2 CH2 CH2N
PB14.Signal=TIM1_CH2N
PB15.Mode=Output Compare3 CH3 CH3N
PB15.Signal=TIM1_CH3N
PB2.GPIOParameters=GPIO_Label
PB2.GPIO_Label=BEMF_A
PB2.Mode=IN12-Single-Ended
PB2.Signal=ADC2_IN12
PB3.Signal=SYS_JTDO-SWO
PB4.GPIOParameters=GPIO_Label
PB4.GPIO_Label=RC_PWM_IN
PB4.Signal=S_TIM3_CH1
PB5.GPIOParameters=GPIO_Label
PB5.GPIO_Label=LED1
PB5.Signal=GPIO_Output
PB6.Signal=USART1_TX
PB7.Signal=USART1_RX
PB9.GPIOParameters=GPIO_Label
PB9.GPIO_Label=LED2
PB9.Signal=GPIO_Output
PC13.GPIOParameters=GPIO_Label
PC13.GPIO_Label=LED3
PC13.Signal=GPIO_Output
PC14-OSC32_IN.GPIOParameters=GPIO_Label
PC14-OSC32_IN.GPIO_Label=LED4
PC14-OSC32_IN.Signal=GPIO_Output
PC15-OSC32_OUT.GPIOParameters=GPIO_Label
PC15-OSC32_OUT.GPIO_Label=LED5
PC15-OSC32_OUT.Signal=GPIO_Output
PF0-OSC_IN.Mode=HSE-External-Oscillator
PF0-OSC_IN.Signal=RCC_OSC_IN
PF1-OSC_OUT.Mode=HSE-External-Oscillator
PF1-OSC_OUT.Signal=RCC_OSC_OUT
RCC.HSE_VALUE=8000000
RCC.SYSCLKFreq_VALUE=168000000
RCC.SYSCLKSource=RCC_SYSCLKSOURCE_PLLCLK
board=custom

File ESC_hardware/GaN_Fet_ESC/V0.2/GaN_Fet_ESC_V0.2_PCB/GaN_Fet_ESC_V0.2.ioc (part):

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Mcu.Name=STM32G473C(B-C-E)Tx
Mcu.Package=LQFP48
Mcu.UserName=STM32G473CETx
PA0.Signal=SharedAnalog_PA0
PA1.Signal=SharedAnalog_PA1
PA10.Signal=S_TIM1_CH3
PA11.Mode=FDCAN_Activate
PA11.Signal=FDCAN1_RX
PA12.Mode=FDCAN_Activate
PA12.Signal=FDCAN1_TX
PA13.Mode=JTAG_4_pins
PA13.Signal=SYS_JTMS-SWDIO
PA14.Mode=JTAG_4_pins
PA14.Signal=SYS_JTCK-SWCLK
PA15.Mode=JTAG_4_pins
PA15.Signal=SYS_JTDI
PA2.Mode=IN3-Single-Ended
PA2.Signal=ADC1_IN3
PA3.Signal=SharedAnalog_PA3
PA4.Signal=GPIO_Input
PA5.Signal=GPIO_Output
PA6.Mode=IN3-Single-Ended
PA6.Signal=ADC2_IN3
PA7.Signal=GPIO_Output
PA8.Signal=S_TIM1_CH1
PA9.Signal=S_TIM1_CH2
PB0.Mode=IN15-Single-Ended
PB0.Signal=ADC1_IN15
PB1.Mode=Standalone-DAC_OUT2-INP
PB1.Signal=OPAMP3_VOUT
PB10.Signal=GPIO_Output
PB11.Mode=IN14-Single-Ended
PB11.Signal=ADC1_IN14
PB12.Mode=IN3-Single-Ended
PB12.Signal=ADC4_IN3
PB13.Mode=IN5-Single-Ended
PB13.Signal=ADC3_IN5
PB14.Mode=PWM Generation2 CH2 CH2N
PB14.Signal=TIM1_CH2N
PB15.Mode=Output Compare3 CH3 CH3N
PB15.Signal=TIM1_CH3N
PB2.Mode=Standalone-DAC_OUT2-INP
PB2.Signal=OPAMP3_VINM
PB3.Mode=JTAG_4_pins
PB3.Signal=SYS_JTDO-SWO
PB4.Signal=S_TIM3_CH1
PB5.Signal=GPIO_Output
PB6.Mode=Asynchronous
PB6.Signal=USART1_TX
PB7.Mode=Asynchronous
PB7.Signal=USART1_RX
PB9.Signal=GPIO_Output
PC13.Mode=Forced Output1 CH1 CH1N
PC13.Signal=TIM1_CH1N
PC14-OSC32_IN.Signal=GPXTI14
PC15-OSC32_OUT.Signal=GPXTI15
PF0-OSC_IN.Mode=HSE-External-Oscillator
PF0-OSC_IN.Signal=RCC_OSC_IN
PF1-OSC_OUT.Mode=HSE-External-Oscillator
PF1-OSC_OUT.Signal=RCC_OSC_OUT
RCC.HSE_VALUE=8000000
RCC.SYSCLKFreq_VALUE=16000000
board=custom

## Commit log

2020-09-27 osc and test
2020-11-21 FreeRTOS added, ADC launched.
2020-12-01 Opamp and DMA added
2021-01-20 Initial non-working FMAC
2022-02-13 Update README.md
    Description added
2022-02-13 0.2 hardware version added; some software experiments
2022-02-13 Resolve conflict
